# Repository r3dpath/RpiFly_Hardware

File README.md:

### RpiFly V3 Hardware

While most of the functionality here has been tested to work theres certainally some marginal design decisions, just beware.

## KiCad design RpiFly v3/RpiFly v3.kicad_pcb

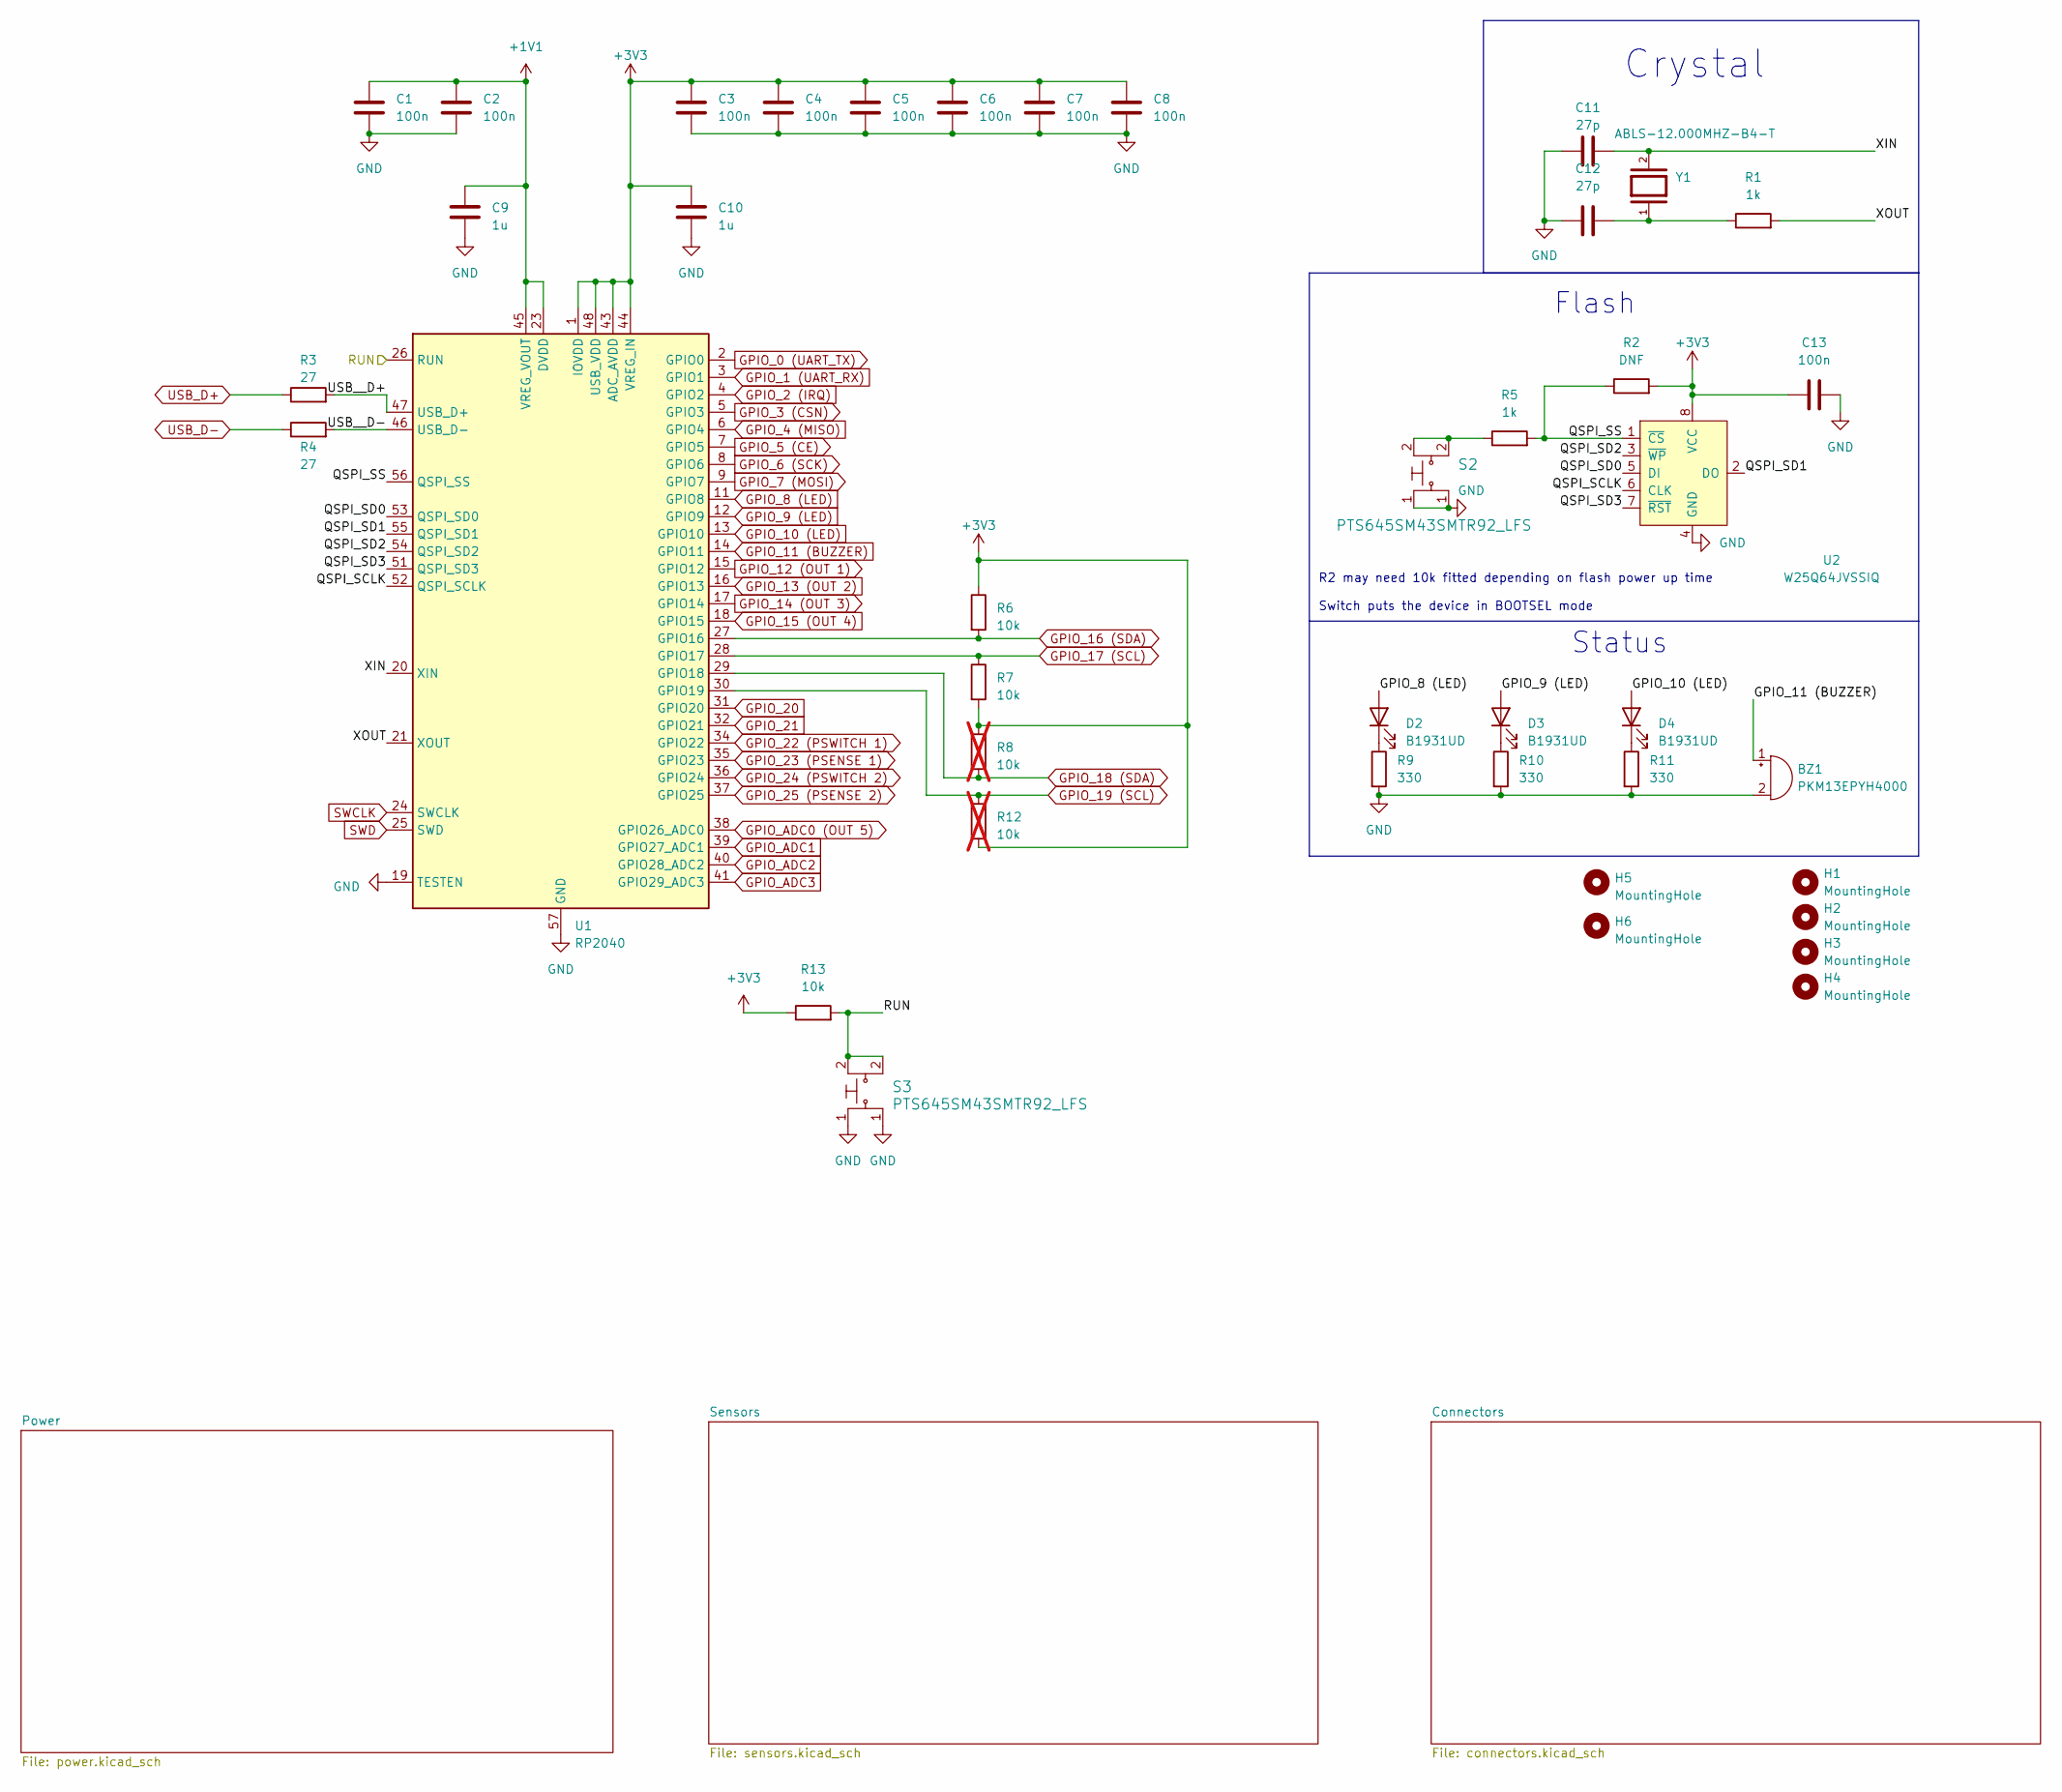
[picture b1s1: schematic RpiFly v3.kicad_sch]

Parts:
BZ1: PKM13EPYH4000
C1, C2, C3, C4, C5, C6, C7, C8, C13: 100n; C_0603_1608Metric
C9, C10: 1u; C_0603_1608Metric
C11, C12: 27p; C_0603_1608Metric
D2, D3, D4: B1931UD; LED_0603_1608Metric
H1, H2, H3, H4: MountingHole; MountingHole_3.2mm_M3_Pad_Via
H5, H6: MountingHole; MountingHole_1.1mm_M1_Pad
R1, R5: 1k; R_0603_1608Metric
R2: DNF; R_0603_1608Metric
R3, R4: 27; R_0603_1608Metric
R6, R7, R13: 10k; R_0603_1608Metric
R8, R12: 10k; R_0603_1608Metric; not fitted
R9, R10, R11: 330; R_0603_1608Metric
S2, S3: PTS645SM43SMTR92_LFS; SW_Push_1P1T_NO_6x6mm_H9.5mm; MPN PTS645SM43SMTR92 LFS; Digi-Key_PN CKN9112CT-ND
U1: RP2040; QFN-56-1EP_7x7mm_P0.4mm_EP3.2x3.2mm
U2: W25Q64JVSSIQ; SOIC-8_5.23x5.23mm_P1.27mm; MPN W25Q32JVSSIQ TR; Digi-Key_PN W25Q32JVSSIQCT-ND
Y1: ABLS-12.000MHZ-B4-T; Crystal_SMD_HC49-SD; PARTREV 02.16.2021

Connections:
+1V1: C1.1, C2.1, C9.1, U1.23 (DVDD), U1.45 (VREG_VOUT), U1.50 (DVDD)
+3V3: C3.1, C4.1, C5.1, C6.1, C7.1, C8.1, C10.1, C13.1, R2.2, R6.1, R7.2, R8.1, R12.2, R13.1, U1.1 (IOVDD), U1.10 (IOVDD), U1.22 (IOVDD), U1.33 (IOVDD), U1.42 (IOVDD), U1.43 (ADC_AVDD), U1.44 (VREG_IN), U1.48 (USB_VDD), U1.49 (IOVDD), U2.8 (VCC); also elsewhere on the board
/QSPI_SCLK: U1.52 (QSPI_SCLK), U2.6 (CLK)
/QSPI_SD0: U1.53 (QSPI_SD0), U2.5 (DI)
/QSPI_SD1: U1.55 (QSPI_SD1), U2.2 (DO)
/QSPI_SD2: U1.54 (QSPI_SD2), U2.3 (~WP)
/QSPI_SD3: U1.51 (QSPI_SD3), U2.7 (~RST)
/QSPI_SS: R2.1, R5.2, U1.56 (QSPI_SS), U2.1 (~CS)
/RUN: R13.2, S3.2, U1.26 (RUN)
/USB__D+: R3.2, U1.47 (USB_D+)
/USB__D-: R4.2, U1.46 (USB_D-)
/XIN: C11.2, U1.20 (XIN), Y1.2
/XOUT: R1.2, U1.21 (XOUT)
GND: BZ1.2 (+), C1.2, C2.2, C3.2, C4.2, C5.2, C6.2, C7.2, C8.2, C9.2, C10.2, C11.1, C12.2, C13.2, H1.1, H2.1, R9.2, R10.2, R11.2, S2.1, S3.1, U1.19 (TESTEN), U1.57 (GND), U2.4 (GND); also elsewhere on the board
GPIO_0 (UART_TX): U1.2 (GPIO0); also elsewhere on the board
GPIO_1 (UART_RX): U1.3 (GPIO1); also elsewhere on the board
GPIO_2 (IRQ): U1.4 (GPIO2); also elsewhere on the board
GPIO_3 (CSN): U1.5 (GPIO3); also elsewhere on the board
GPIO_4 (MISO): U1.6 (GPIO4); also elsewhere on the board
GPIO_5 (CE): U1.7 (GPIO5); also elsewhere on the board
GPIO_6 (SCK): U1.8 (GPIO6); also elsewhere on the board
GPIO_7 (MOSI): U1.9 (GPIO7); also elsewhere on the board
GPIO_8 (LED): D2.2 (A), U1.11 (GPIO8)
GPIO_9 (LED): D3.2 (A), U1.12 (GPIO9)
GPIO_10 (LED): D4.2 (A), U1.13 (GPIO10)
GPIO_11 (BUZZER): BZ1.1 (-), U1.14 (GPIO11)
GPIO_12 (OUT 1): U1.15 (GPIO12); also elsewhere on the board
GPIO_13 (OUT 2): U1.16 (GPIO13); also elsewhere on the board
GPIO_14 (OUT 3): U1.17 (GPIO14); also elsewhere on the board
GPIO_15 (OUT 4): U1.18 (GPIO15); also elsewhere on the board
GPIO_16 (SDA): R6.2, U1.27 (GPIO16); also elsewhere on the board
GPIO_17 (SCL): R7.1, U1.28 (GPIO17); also elsewhere on the board
GPIO_18 (SDA): R8.2, U1.29 (GPIO18); also elsewhere on the board
GPIO_19 (SCL): R12.1, U1.30 (GPIO19); also elsewhere on the board
GPIO_20: U1.31 (GPIO20)
GPIO_21: U1.32 (GPIO21)
GPIO_22 (PSWITCH 1): U1.34 (GPIO22); also elsewhere on the board
GPIO_23 (PSENSE 1): U1.35 (GPIO23); also elsewhere on the board
GPIO_24 (PSWITCH 2): U1.36 (GPIO24); also elsewhere on the board
GPIO_25 (PSENSE 2): U1.37 (GPIO25); also elsewhere on the board
GPIO_ADC0 (OUT 5): U1.38 (GPIO26_ADC0); also elsewhere on the board
GPIO_ADC1: U1.39 (GPIO27_ADC1)
GPIO_ADC2: U1.40 (GPIO28_ADC2)
GPIO_ADC3: U1.41 (GPIO29_ADC3)
unnamed: C12.1, R1.1, Y1.1
unnamed: D2.1 (K), R9.1
unnamed: D3.1 (K), R10.1
unnamed: D4.1 (K), R11.1
unnamed: R5.1, S2.2
SWCLK: U1.24 (SWCLK); also elsewhere on the board
SWD: U1.25 (SWD); also elsewhere on the board
USB_D+: R3.1; also elsewhere on the board
USB_D-: R4.1; also elsewhere on the board

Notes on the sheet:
R2 may need 10k fitted depending on flash power up time Switch puts the device in BOOTSEL mode
Flash
Crystal
Status

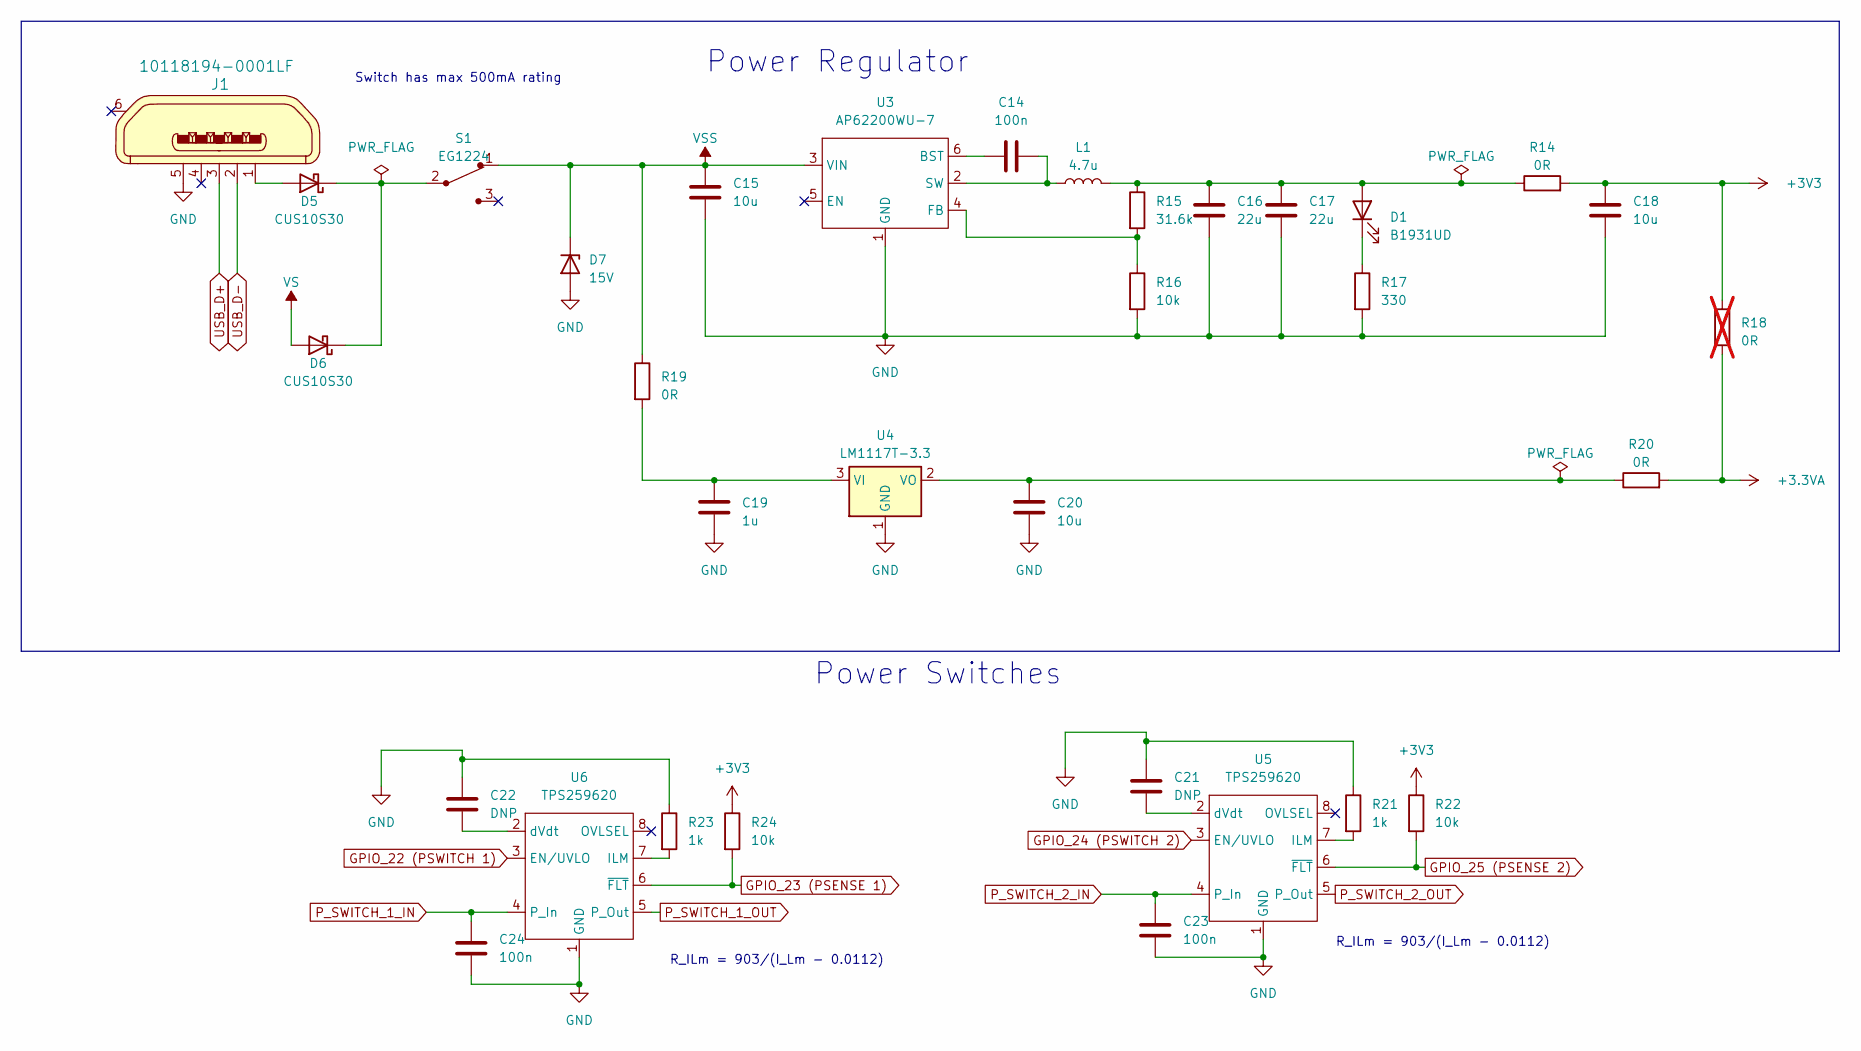
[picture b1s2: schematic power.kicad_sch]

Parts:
C14, C23, C24: 100n; C_0603_1608Metric
C15, C18, C20: 10u; C_0603_1608Metric
C16, C17: 22u; C_0603_1608Metric
C19: 1u; C_0603_1608Metric
C21, C22: DNP; C_0603_1608Metric
D1: B1931UD; D_0603_1608Metric
D5, D6: CUS10S30; D_SOD-323
D7: 15V; D_DO-41_SOD81_P7.62mm_Horizontal
J1: 10118194-0001LF; USB_Micro-B_Amphenol_10118194_Horizontal; MPN 10118194-0001LF; Digi-Key_PN 609-4618-1-ND
L1: 4.7u; L_Taiyo-Yuden_NR-60xx
R14, R19, R20: 0R; R_0603_1608Metric
R15: 31.6k; R_0603_1608Metric
R16, R22, R24: 10k; R_0603_1608Metric
R17: 330; R_0603_1608Metric
R18: 0R; R_0603_1608Metric; not fitted
R21, R23: 1k; R_0603_1608Metric
S1: EG1224; SW_E-Switch_EG1224_SPDT_Angled; MPN EG1218; Digi-Key_PN EG1903-ND
U3: AP62200WU-7; TSOT-23-6
U4: LM1117T-3.3; TO-220-3_Horizontal_TabDown
U5, U6: TPS259620; Texas_R-PDSO-G8_EP2.95x4.9mm_Mask2.4x3.1mm_ThermalVias

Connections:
+3.3VA: R18.2, R20.2; also elsewhere on the board
+3V3: C18.1, R14.2, R18.1, R22.1, R24.1; also elsewhere on the board
GND: C15.1, C16.2, C17.2, C18.2, C19.2, C20.2, C21.1, C22.1, C23.2, C24.2, D7.2 (A), J1.5, R16.2, R17.2, R21.1, R23.1, U3.1 (GND), U4.1 (GND), U5.1 (GND), U6.1 (GND); also elsewhere on the board
GPIO_22 (PSWITCH 1): U6.3 (EN/UVLO); also elsewhere on the board
GPIO_23 (PSENSE 1): R24.2, U6.6 (~FLT); also elsewhere on the board
GPIO_24 (PSWITCH 2): U5.3 (EN/UVLO); also elsewhere on the board
GPIO_25 (PSENSE 2): R22.2, U5.6 (~FLT); also elsewhere on the board
unnamed: C16.1, C17.1, D1.2 (A), L1.2, R14.1, R15.1
unnamed: D1.1 (K), R17.1
unnamed: D5.2 (A), J1.1
unnamed: D5.1 (K), D6.1 (K), S1.2
unnamed: C14.1, U3.6 (BST)
unnamed: R15.2, R16.1, U3.4 (FB)
unnamed: C14.2, L1.1, U3.2 (SW)
unnamed: C19.1, R19.2, U4.3 (VI)
unnamed: C20.1, R20.1, U4.2 (VO)
unnamed: R21.2, U5.7 (ILM)
unnamed: C21.2, U5.2 (dVdt)
unnamed: R23.2, U6.7 (ILM)
unnamed: C22.2, U6.2 (dVdt)
P_SWITCH_1_IN: C24.1, U6.4 (P_In); also elsewhere on the board
P_SWITCH_1_OUT: U6.5 (P_Out); also elsewhere on the board
P_SWITCH_2_IN: C23.1, U5.4 (P_In); also elsewhere on the board
P_SWITCH_2_OUT: U5.5 (P_Out); also elsewhere on the board
USB_D+: J1.3; also elsewhere on the board
USB_D-: J1.2; also elsewhere on the board
VS: D6.2 (A); also elsewhere on the board
VSS: C15.2, D7.1 (K), R19.1, S1.1, U3.3 (VIN)

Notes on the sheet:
Switch has max 500mA rating
Power Switches
R_ILm = 903/(I_Lm - 0.0112)
Power Regulator

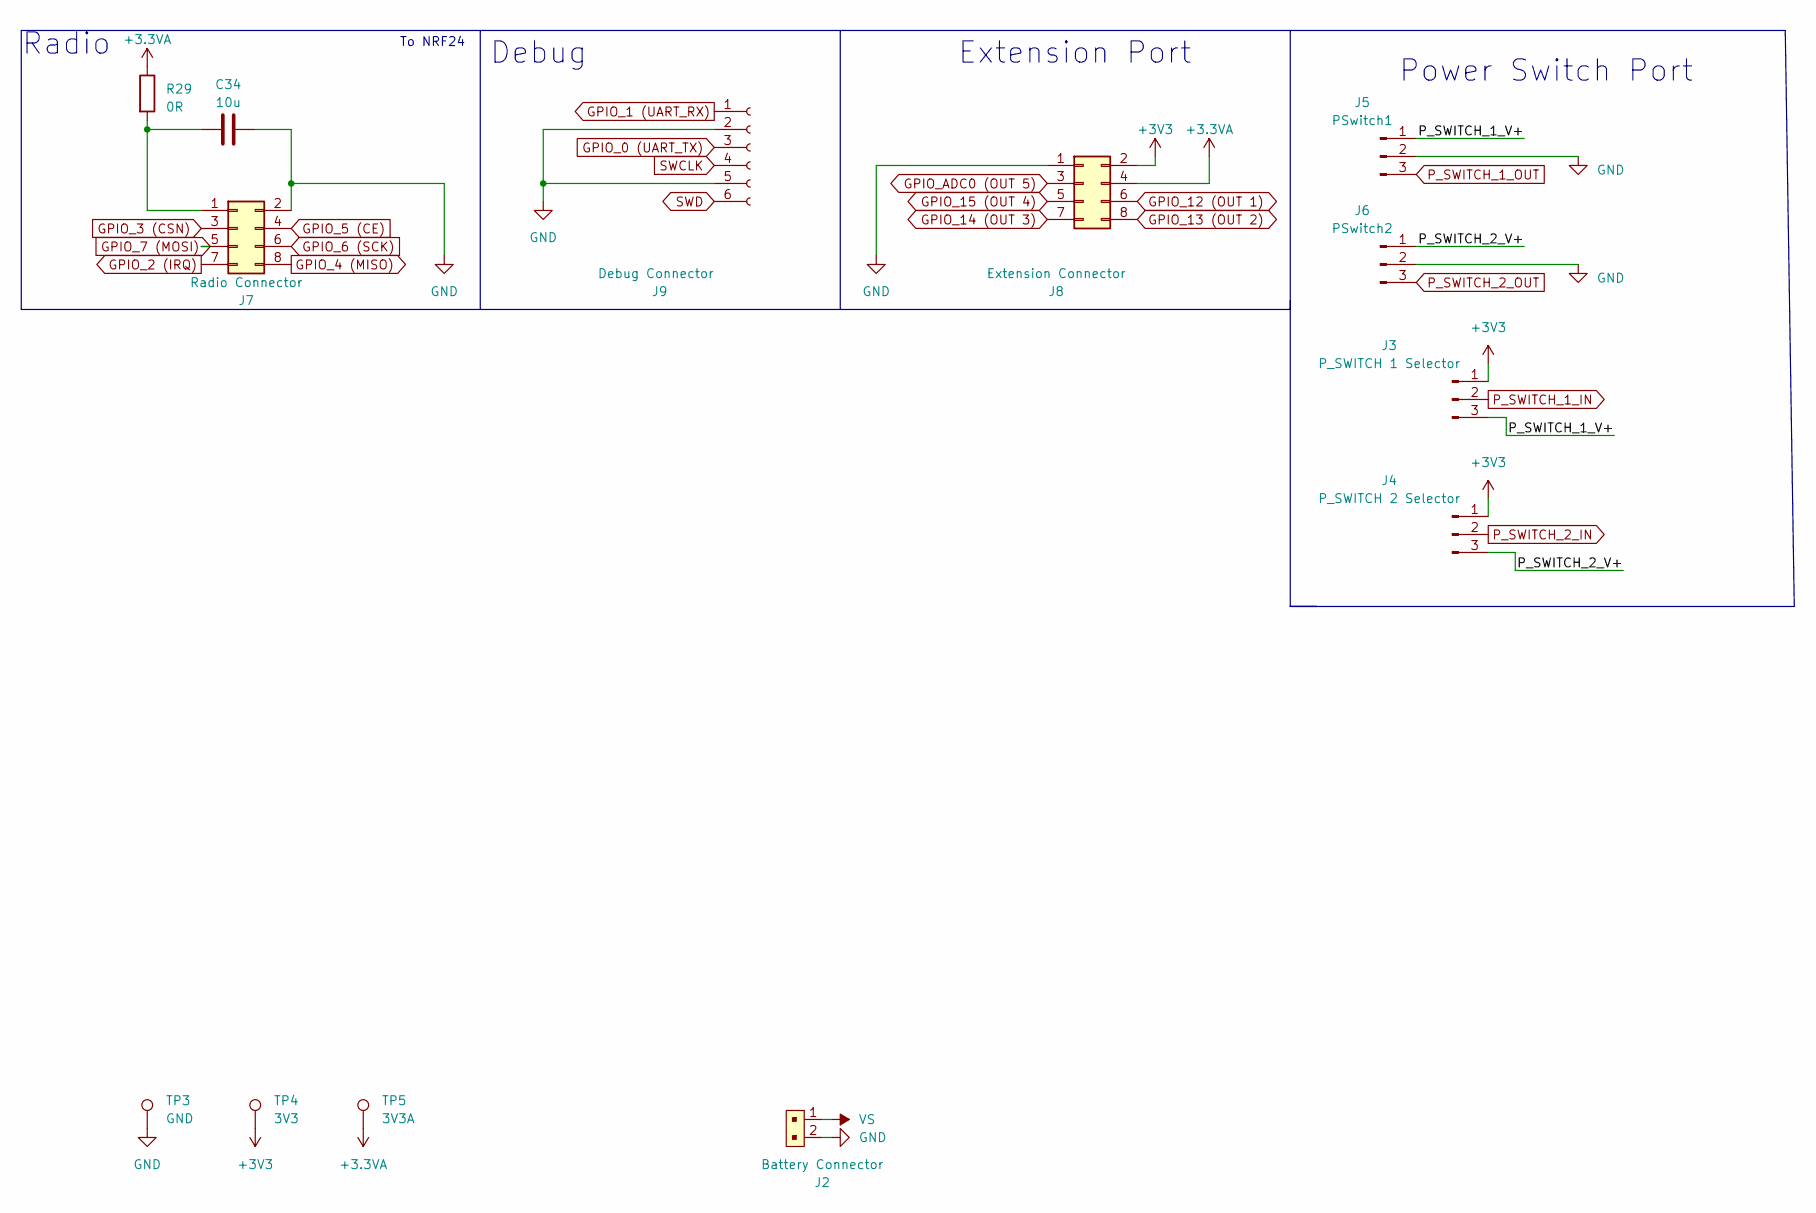
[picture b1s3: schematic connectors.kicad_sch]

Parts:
C34: 10u; C_0603_1608Metric
J2: Battery Connector; JST_PH_S2B-PH-K_1x02_P2.00mm_Horizontal
J3: P_SWITCH 1 Selector; PinHeader_1x03_P2.54mm_Vertical
J4: P_SWITCH 2 Selector; PinHeader_1x03_P2.54mm_Vertical
J5: PSwitch1; JST_PH_S3B-PH-K_1x03_P2.00mm_Horizontal
J6: PSwitch2; JST_PH_S3B-PH-K_1x03_P2.00mm_Horizontal
J7: Radio Connector; PinSocket_2x04_P2.54mm_Vertical
J8: Extension Connector; PinSocket_2x04_P2.54mm_Vertical
J9: Debug Connector; JST_SH_SM06B-SRSS-TB_1x06-1MP_P1.00mm_Horizontal
R29: 0R; R_0603_1608Metric
TP3: GND; TestPoint_Pad_D1.0mm
TP4: 3V3; TestPoint_Pad_D1.0mm
TP5: 3V3A; TestPoint_Pad_D1.0mm

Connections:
+3.3VA: J8.4, R29.1, TP5.1; also elsewhere on the board
+3V3: J3.1, J4.1, J8.2, TP4.1; also elsewhere on the board
/Connectors/P_SWITCH_1_V+: J3.3, J5.1
/Connectors/P_SWITCH_2_V+: J4.3, J6.1
GND: C34.2, J2.2, J5.2, J6.2, J7.2, J8.1, J9.2, J9.5, TP3.1; also elsewhere on the board
GPIO_0 (UART_TX): J9.3; also elsewhere on the board
GPIO_1 (UART_RX): J9.1; also elsewhere on the board
GPIO_2 (IRQ): J7.7; also elsewhere on the board
GPIO_3 (CSN): J7.3; also elsewhere on the board
GPIO_4 (MISO): J7.8; also elsewhere on the board
GPIO_5 (CE): J7.4; also elsewhere on the board
GPIO_6 (SCK): J7.6; also elsewhere on the board
GPIO_7 (MOSI): J7.5; also elsewhere on the board
GPIO_12 (OUT 1): J8.6; also elsewhere on the board
GPIO_13 (OUT 2): J8.8; also elsewhere on the board
GPIO_14 (OUT 3): J8.7; also elsewhere on the board
GPIO_15 (OUT 4): J8.5; also elsewhere on the board
GPIO_ADC0 (OUT 5): J8.3; also elsewhere on the board
unnamed: C34.1, J7.1, R29.2
P_SWITCH_1_IN: J3.2; also elsewhere on the board
P_SWITCH_1_OUT: J5.3; also elsewhere on the board
P_SWITCH_2_IN: J4.2; also elsewhere on the board
P_SWITCH_2_OUT: J6.3; also elsewhere on the board
SWCLK: J9.4; also elsewhere on the board
SWD: J9.6; also elsewhere on the board
VS: J2.1; also elsewhere on the board

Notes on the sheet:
Extension Port
Power Switch Port
Radio
Debug
To NRF24

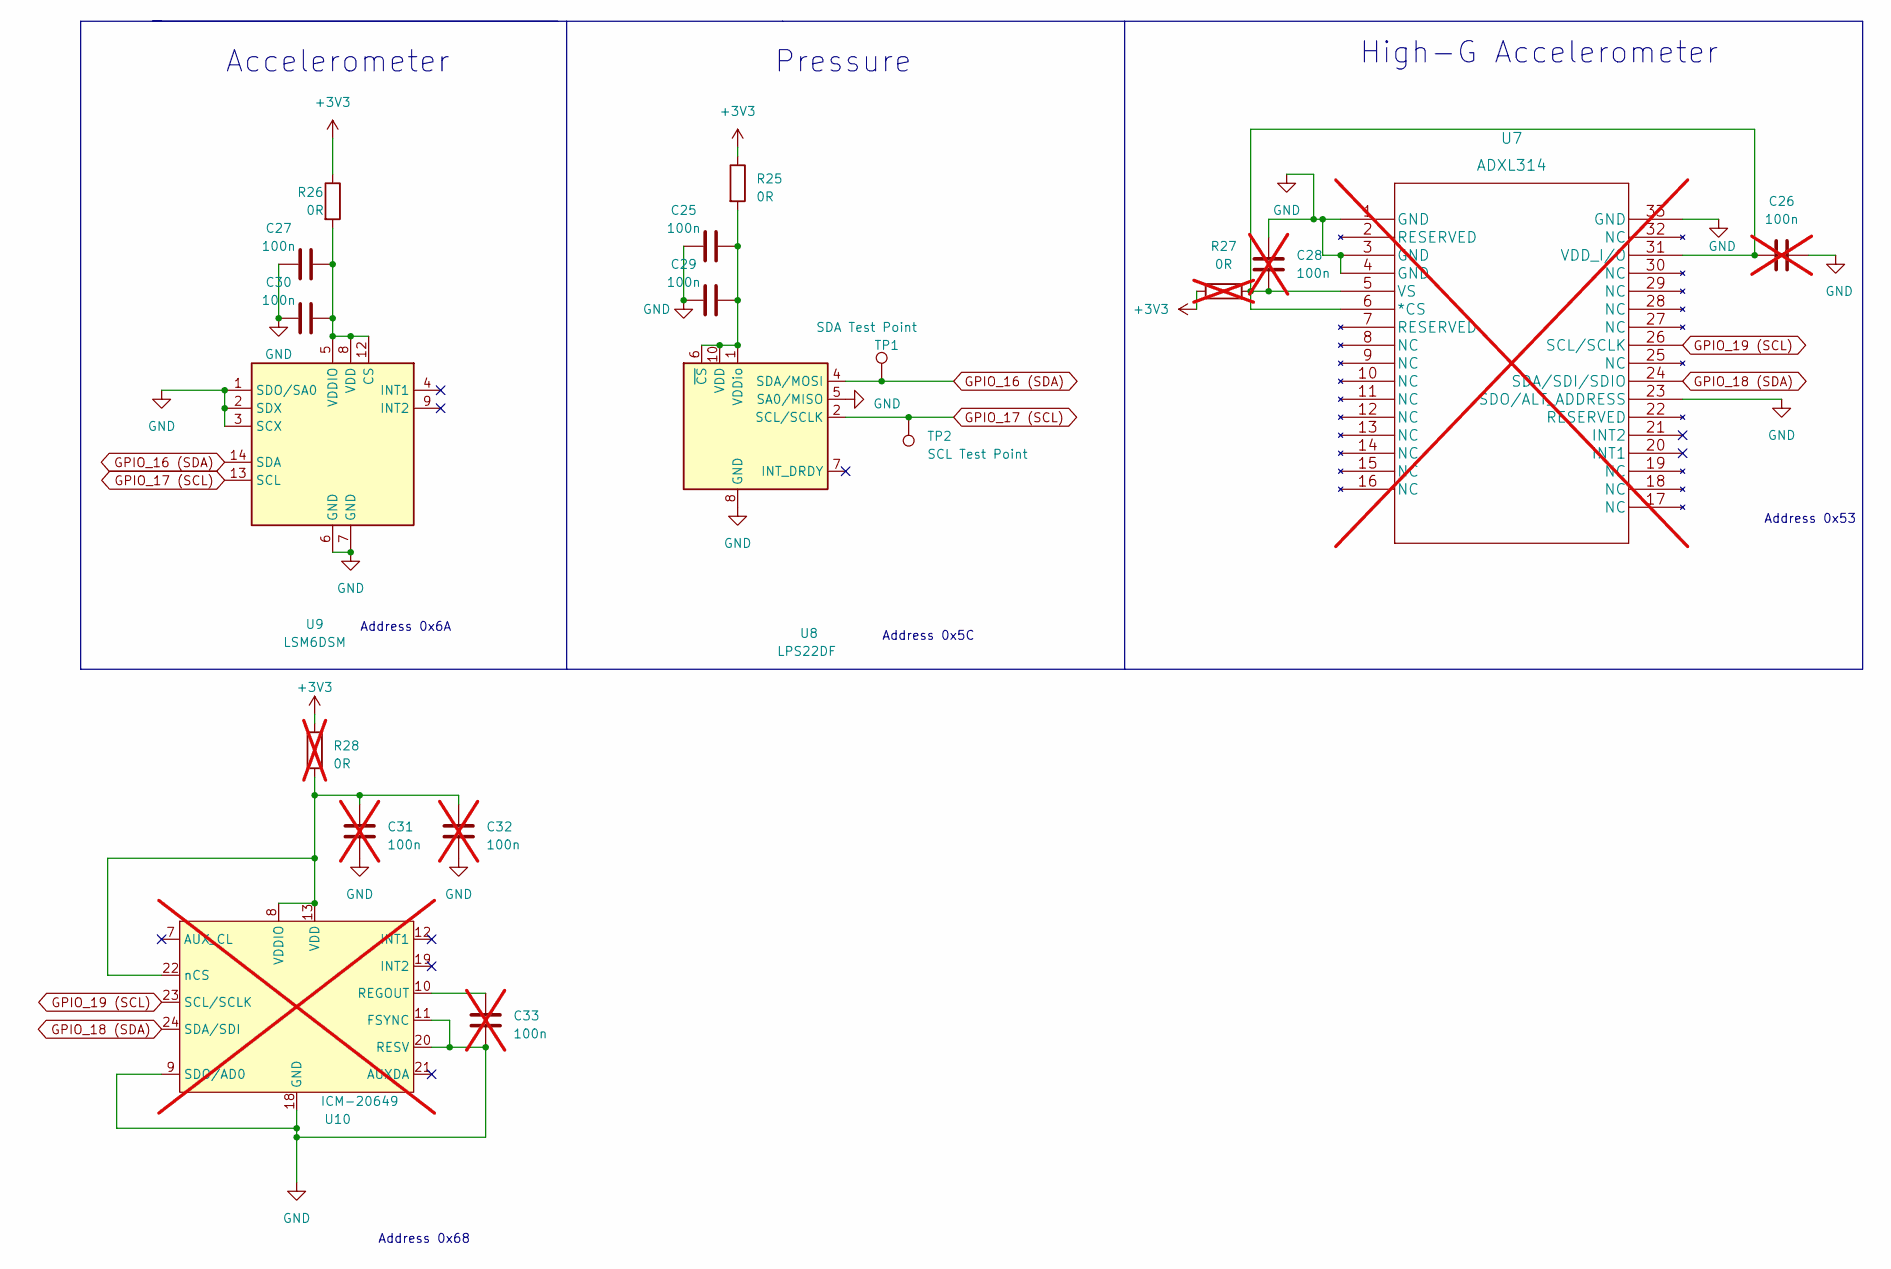
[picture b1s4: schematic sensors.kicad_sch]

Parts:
C25, C27, C29, C30: 100n; C_0603_1608Metric
C26, C28, C31, C32, C33: 100n; C_0603_1608Metric; not fitted
R25, R26: 0R; R_0603_1608Metric
R27, R28: 0R; R_0603_1608Metric; not fitted
TP1: SDA Test Point; TestPoint_Pad_D1.0mm
TP2: SCL Test Point; TestPoint_Pad_D1.0mm
U7: ADXL314; LFCSP-32-1EP_5x5mm_P0.5mm_EP3.6x3.6mm; not fitted
U8: LPS22DF; ST_HLGA-10_2.5x2.5mm_P0.6mm_LayoutBorder3x2y
U9: LSM6DSM; LGA-14_3x2.5mm_P0.5mm_LayoutBorder3x4y
U10: ICM-20649; QFN-24-1EP_3x3mm_P0.4mm_EP1.75x1.6mm; not fitted

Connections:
+3V3: R25.1, R26.1, R27.1, R28.1; also elsewhere on the board
GND: C25.1, C26.2, C27.1, C28.1, C29.1, C30.1, C31.2, C32.1, C33.2, U7.1 (GND), U7.3 (GND), U7.4 (GND), U7.23 (SDO/ALT_ADDRESS), U7.33 (GND), U8.3 (GND), U8.5 (SA0/MISO), U8.8 (GND), U8.9 (GND), U9.1 (SDO/SA0), U9.2 (SDX), U9.3 (SCX), U9.6 (GND), U9.7 (GND), U10.9 (SDO/AD0), U10.11 (FSYNC), U10.18 (GND), U10.20 (RESV); also elsewhere on the board
GPIO_16 (SDA): TP1.1, U8.4 (SDA/MOSI), U9.14 (SDA); also elsewhere on the board
GPIO_17 (SCL): TP2.1, U8.2 (SCL/SCLK), U9.13 (SCL); also elsewhere on the board
GPIO_18 (SDA): U7.24 (SDA/SDI/SDIO), U10.24 (SDA/SDI); also elsewhere on the board
GPIO_19 (SCL): U7.26 (SCL/SCLK), U10.23 (SCL/SCLK); also elsewhere on the board
unnamed: C26.1, C28.2, R27.2, U7.5 (VS), U7.6 (*CS), U7.31 (VDD_I/O)
unnamed: C25.2, C29.2, R25.2, U8.1 (VDDio), U8.6 (~CS), U8.10 (VDD)
unnamed: C27.2, C30.2, R26.2, U9.5 (VDDIO), U9.8 (VDD), U9.12 (CS)
unnamed: C33.1, U10.10 (REGOUT)
unnamed: C31.1, C32.2, R28.2, U10.8 (VDDIO), U10.13 (VDD), U10.22 (nCS)

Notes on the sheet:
Accelerometer
High-G Accelerometer
Pressure
Address 0x53
Address 0x68
Address 0x6A
Address 0x5C

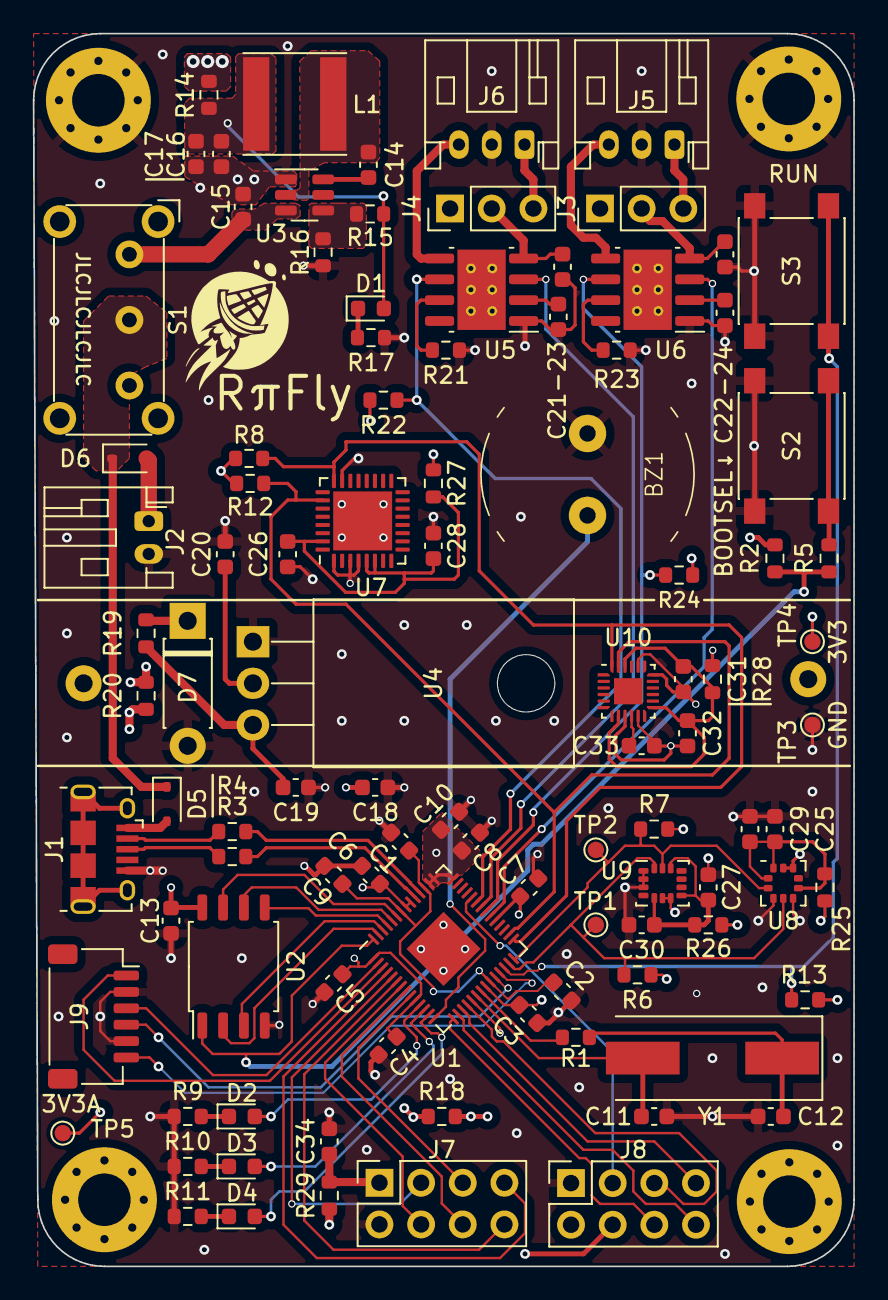
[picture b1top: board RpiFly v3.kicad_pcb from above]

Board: 4 copper layers, 50.0 x 75.2 mm, 106 parts (1 on the bottom side), 76 nets.

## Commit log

2024-03-12 initial
